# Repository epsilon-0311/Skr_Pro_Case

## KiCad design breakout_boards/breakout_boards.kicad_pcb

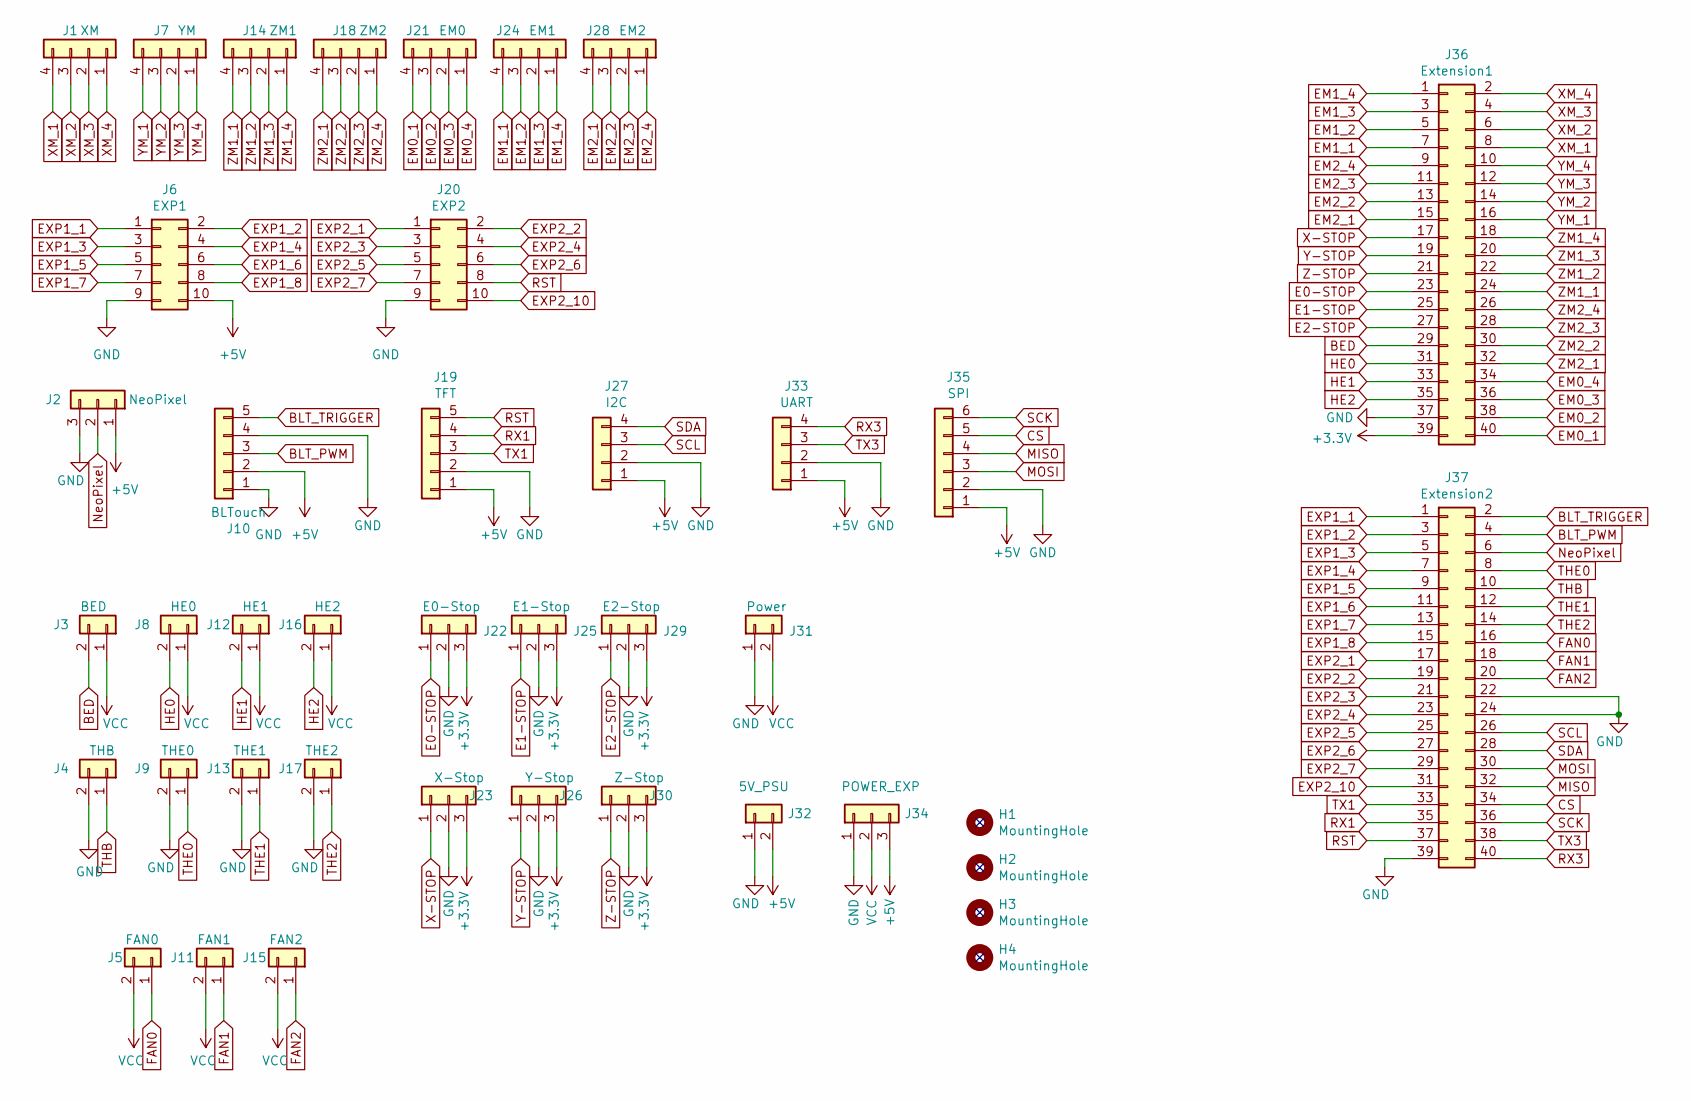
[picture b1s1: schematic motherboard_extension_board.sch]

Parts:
H1, H2, H3, H4: MountingHole; MountingHole_3.2mm_M3_DIN965
J1: XM; JST_XH_B4B-XH-A_1x04_P2.50mm_Vertical
J2: NeoPixel; PhoenixContact_MSTBA_2,5_3-G_1x03_P5.00mm_Horizontal
J3: BED; JST_XH_B2B-XH-A_1x02_P2.50mm_Vertical
J4: THB; JST_XH_B2B-XH-A_1x02_P2.50mm_Vertical
J5: FAN0; JST_XH_B2B-XH-A_1x02_P2.50mm_Vertical
J6: EXP1; IDC-Header_2x05_P2.54mm_Vertical
J7: YM; JST_XH_B4B-XH-A_1x04_P2.50mm_Vertical
J8: HE0; JST_XH_B2B-XH-A_1x02_P2.50mm_Vertical
J9: THE0; JST_XH_B2B-XH-A_1x02_P2.50mm_Vertical
J10: BLTouch; JST_XH_B5B-XH-A_1x05_P2.50mm_Vertical
J11: FAN1; JST_XH_B2B-XH-A_1x02_P2.50mm_Vertical
J12: HE1; JST_XH_B2B-XH-A_1x02_P2.50mm_Vertical
J13: THE1; JST_XH_B2B-XH-A_1x02_P2.50mm_Vertical
J14: ZM1; JST_XH_B4B-XH-A_1x04_P2.50mm_Vertical
J15: FAN2; JST_XH_B2B-XH-A_1x02_P2.50mm_Vertical
J16: HE2; JST_XH_B2B-XH-A_1x02_P2.50mm_Vertical
J17: THE2; JST_XH_B2B-XH-A_1x02_P2.50mm_Vertical
J18: ZM2; JST_XH_B4B-XH-A_1x04_P2.50mm_Vertical
J19: TFT; JST_XH_B5B-XH-A_1x05_P2.50mm_Vertical
J20: EXP2; IDC-Header_2x05_P2.54mm_Vertical
J21: EM0; JST_XH_B4B-XH-A_1x04_P2.50mm_Vertical
J22: E0-Stop; JST_XH_B3B-XH-A_1x03_P2.50mm_Vertical
J23: X-Stop; JST_XH_B3B-XH-A_1x03_P2.50mm_Vertical
J24: EM1; JST_XH_B4B-XH-A_1x04_P2.50mm_Vertical
J25: E1-Stop; JST_XH_B3B-XH-A_1x03_P2.50mm_Vertical
J26: Y-Stop; JST_XH_B3B-XH-A_1x03_P2.50mm_Vertical
J27: I2C; JST_XH_B4B-XH-A_1x04_P2.50mm_Vertical
J28: EM2; JST_XH_B4B-XH-A_1x04_P2.50mm_Vertical
J29: E2-Stop; JST_XH_B3B-XH-A_1x03_P2.50mm_Vertical
J30: Z-Stop; JST_XH_B3B-XH-A_1x03_P2.50mm_Vertical
J31: Power; PhoenixContact_MSTBA_2,5_2-G_1x02_P5.00mm_Horizontal
J32: 5V_PSU; PhoenixContact_MSTBA_2,5_2-G_1x02_P5.00mm_Horizontal
J33: UART; JST_XH_B4B-XH-A_1x04_P2.50mm_Vertical
J34: POWER_EXP; PhoenixContact_MSTBA_2,5_3-G_1x03_P5.00mm_Horizontal
J35: SPI; JST_XH_B6B-XH-A_1x06_P2.50mm_Vertical
J36: Extension1; IDC-Header_2x20_P2.54mm_Vertical
J37: Extension2; IDC-Header_2x20_P2.54mm_Vertical

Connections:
+3V3: J22.3, J23.3, J25.3, J26.3, J29.3, J30.3, J36.39
+5V: J2.1, J6.10, J10.2, J19.1, J27.1, J32.2, J33.1, J34.3, J35.1
BED: J3.2, J36.29
BLT_PWM: J10.3, J37.4
BLT_TRIGGER: J10.5, J37.2
CS: J35.5, J37.34
E0-STOP: J22.1, J36.23
E1-STOP: J25.1, J36.25
E2-STOP: J29.1, J36.27
EM0_1: J21.4, J36.40
EM0_2: J21.3, J36.38
EM0_3: J21.2, J36.36
EM0_4: J21.1, J36.34
EM1_1: J24.4, J36.7
EM1_2: J24.3, J36.5
EM1_3: J24.2, J36.3
EM1_4: J24.1, J36.1
EM2_1: J28.4, J36.15
EM2_2: J28.3, J36.13
EM2_3: J28.2, J36.11
EM2_4: J28.1, J36.9
EXP1_1: J6.1, J37.1
EXP1_2: J6.2, J37.3
EXP1_3: J6.3, J37.5
EXP1_4: J6.4, J37.7
EXP1_5: J6.5, J37.9
EXP1_6: J6.6, J37.11
EXP1_7: J6.7, J37.13
EXP1_8: J6.8, J37.15
EXP2_1: J20.1, J37.17
EXP2_2: J20.2, J37.19
EXP2_3: J20.3, J37.21
EXP2_4: J20.4, J37.23
EXP2_5: J20.5, J37.25
EXP2_6: J20.6, J37.27
EXP2_7: J20.7, J37.29
EXP2_10: J20.10, J37.31
FAN0: J5.1, J37.16
FAN1: J11.1, J37.18
FAN2: J15.1, J37.20
GND: J2.3, J4.2, J6.9, J9.2, J10.1, J10.4, J13.2, J17.2, J19.2, J20.9, J22.2, J23.2, J25.2, J26.2, J27.2, J29.2, J30.2, J31.1, J32.1, J33.2, J34.1, J35.2, J36.37, J37.22, J37.24, J37.39
HE0: J8.2, J36.31
HE1: J12.2, J36.33
HE2: J16.2, J36.35
MISO: J35.4, J37.32
MOSI: J35.3, J37.30
NeoPixel: J2.2, J37.6
RST: J19.5, J20.8, J37.37
RX1: J19.4, J37.35
RX3: J33.4, J37.40
SCK: J35.6, J37.36
SCL: J27.3, J37.26
SDA: J27.4, J37.28
THB: J4.1, J37.10
THE0: J9.1, J37.8
THE1: J13.1, J37.12
THE2: J17.1, J37.14
TX1: J19.3, J37.33
TX3: J33.3, J37.38
VCC: J3.1, J5.2, J8.1, J11.2, J12.1, J15.2, J16.1, J31.2, J34.2
X-STOP: J23.1, J36.17
XM_1: J1.4, J36.8
XM_2: J1.3, J36.6
XM_3: J1.2, J36.4
XM_4: J1.1, J36.2
Y-STOP: J26.1, J36.19
YM_1: J7.4, J36.16
YM_2: J7.3, J36.14
YM_3: J7.2, J36.12
YM_4: J7.1, J36.10
Z-STOP: J30.1, J36.21
ZM1_1: J14.4, J36.24
ZM1_2: J14.3, J36.22
ZM1_3: J14.2, J36.20
ZM1_4: J14.1, J36.18
ZM2_1: J18.4, J36.32
ZM2_2: J18.3, J36.30
ZM2_3: J18.2, J36.28
ZM2_4: J18.1, J36.26

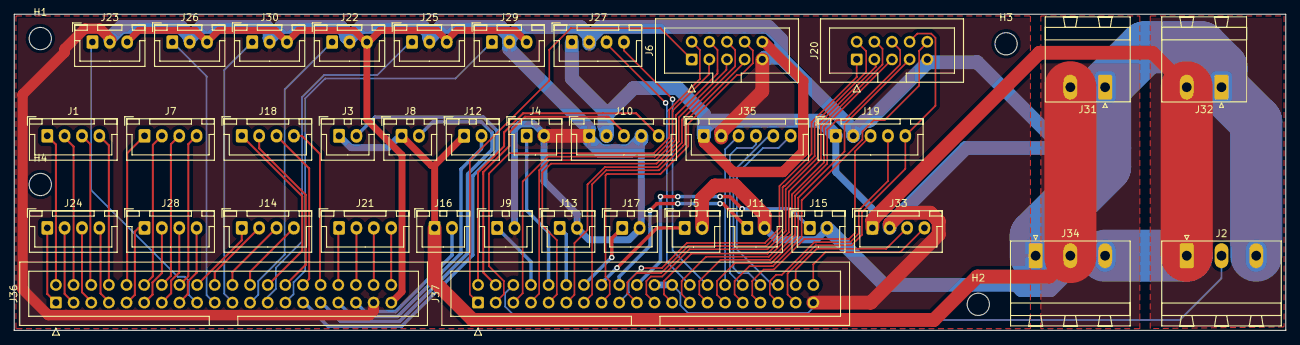
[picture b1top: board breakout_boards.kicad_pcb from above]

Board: 2 copper layers, 183.0 x 45.5 mm, 41 parts (0 on the bottom side), 79 nets.

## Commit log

2020-01-25 added first draft
2020-01-25 updated electronics duct
2020-01-26 model of single parts
2020-01-26 added left side for case
2020-02-02 updated case
2020-02-04 added back case
2020-02-09 added additional versioning of designs
2020-02-09 exports of V2
2020-02-18 started with design version 3
2020-04-04 updated design
2021-07-10 updated structure, added pcb
2021-07-10 updated schematics and pcb
2021-11-23 added gitignore for exports
2021-11-23 removed exports
2021-11-23 added imports
2021-11-23 changed mounting hole footprint and connector jst eh to jst xh
